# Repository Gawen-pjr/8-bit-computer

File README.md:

# 8-bit-computer
Home made 8 bit computer built from discreet logic components

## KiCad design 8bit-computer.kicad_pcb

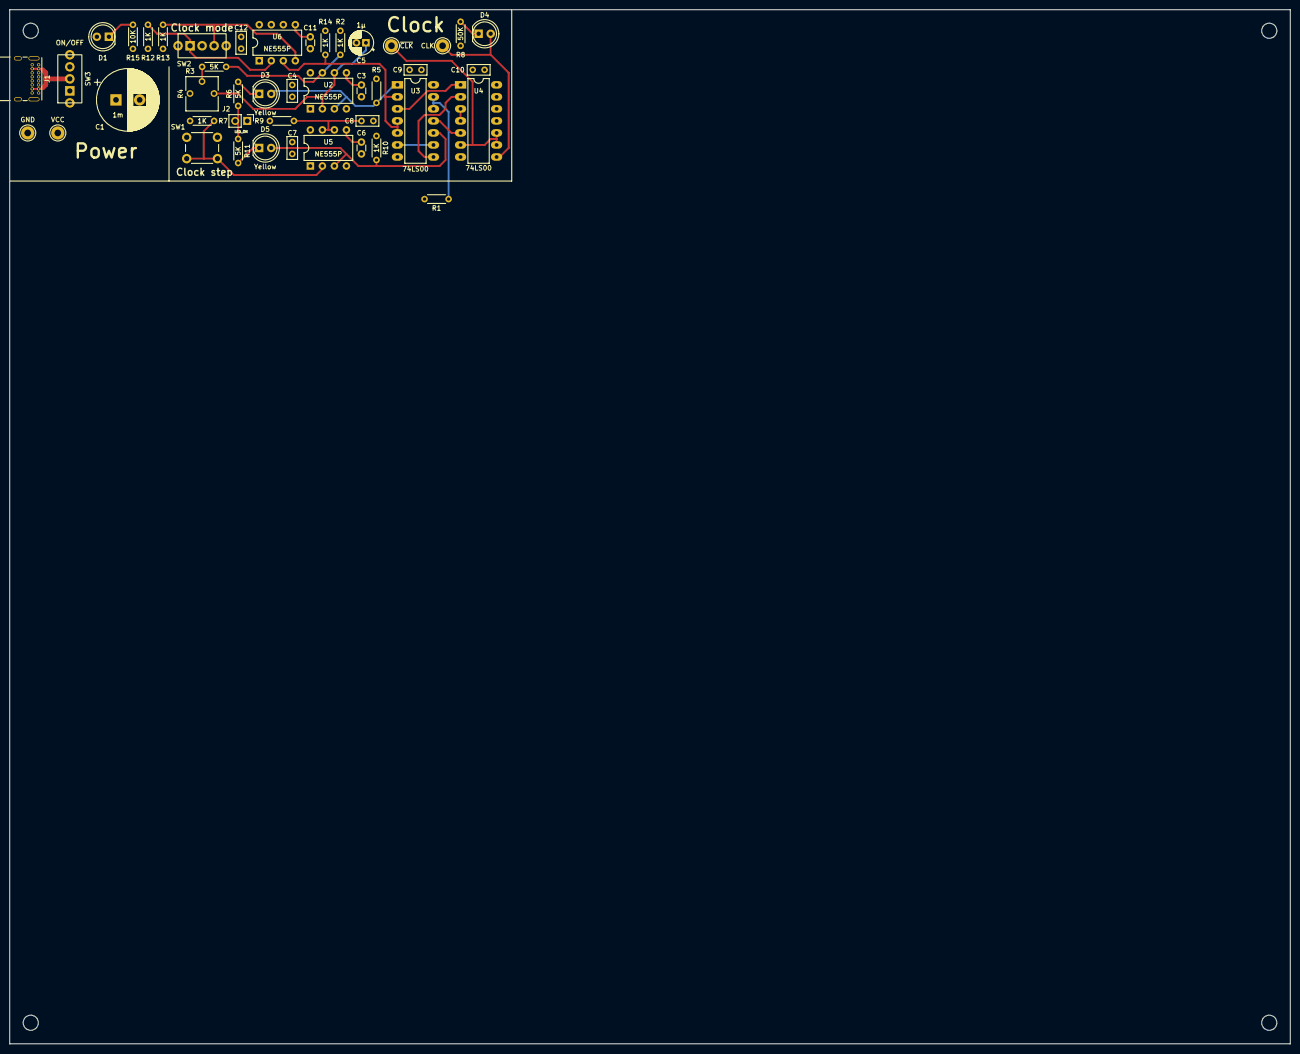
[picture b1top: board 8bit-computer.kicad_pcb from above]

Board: 4 copper layers, 270.5 x 218.4 mm, 48 parts (0 on the bottom side), 29 nets.

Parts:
C1: 1m; CP_Radial_D13.0mm_P5.00mm
C3, C6, C11: 17n; C_Disc_D3.0mm_W1.6mm_P2.50mm
C4, C7, C8, C9, C10, C12: 0.1µ; C_Rect_L4.6mm_W2.0mm_P2.50mm_MKS02_FKP02
C5: 1µ; CP_Radial_D5.0mm_P2.00mm
D1: Red; LED_D5.0mm
D3, D5: Yellow; LED_D5.0mm
D4: Blue; LED_D5.0mm
J1: Power connector; USB_C_Receptacle_GCT_USB4085
J2: LED_ON; PinHeader_1x02_P2.54mm_Vertical
MH1, MH2, MH3, MH4: MountingHole_3.2mm_M3
R1, R2, R5, R7, R10, R12, R13, R14: 1K; R_Axial_DIN0204_L3.6mm_D1.6mm_P5.08mm_Horizontal
R3, R6, R11: 5K; R_Axial_DIN0204_L3.6mm_D1.6mm_P5.08mm_Horizontal
R4: 1.5M; Potentiometer_Vishay_T73YP_Vertical
R8: 50K; R_Axial_DIN0204_L3.6mm_D1.6mm_P5.08mm_Horizontal
R9: 1M; R_Axial_DIN0204_L3.6mm_D1.6mm_P5.08mm_Horizontal
R15: 10K; R_Axial_DIN0204_L3.6mm_D1.6mm_P5.08mm_Horizontal
SW1: Clock step; SW_PUSH_6mm
SW2: Clock mode; MC8MSLP1B06VS2QES
SW3: ON/OFF; MC8MSLP1B06VS2QES
TP1: GND; TestPoint_Loop_D2.60mm_Drill1.4mm_Beaded
TP2: VCC; TestPoint_Loop_D2.60mm_Drill1.4mm_Beaded
TP3: ~{CLK}; TestPoint_Loop_D2.60mm_Drill1.4mm_Beaded
TP4: CLK; TestPoint_Loop_D2.60mm_Drill1.4mm_Beaded
U2, U5, U6: NE555P; DIP-8_W7.62mm
U3, U4: 74LS00; DIP-14_W7.62mm_LongPads

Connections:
+5V: J1.A4 (VBUS), J1.A9 (VBUS), J1.B4 (VBUS), J1.B9 (VBUS), SW3.2 (B)
/Clock/Clk_A: D3.2 (A), R5.2, U2.3 (Q), U3.1
/Clock/Clk_M: D5.2 (A), R10.2, U3.10, U5.3 (Q)
/Clock/HLT: R1.1, U3.12, U3.13
/Clock/LEDs: J2.2, R6.1, R11.1
/Clock/Mode: R14.2, U3.2, U3.4, U3.5, U6.3 (Q)
CLK: D4.2 (A), TP4.1, U4.8
GND: C1.2, C3.2, C4.2, C5.2, C6.2, C7.2, C8.2, C9.2, C10.2, C11.2, C12.2, J1.A1 (GND), J1.A12 (GND), J1.B1 (GND), J1.B12 (GND), J1.S1 (SHIELD), J2.1, R1.2, R8.1, R15.2, SW1.1, SW2.2 (B), TP1.1, U2.1 (GND), U3.7 (GND), U4.7 (GND), U5.1 (GND), U6.1 (GND), U6.6 (THR)
unnamed: C3.1, U2.5 (CV)
unnamed: C5.1, R4.1, U2.2 (TR), U2.6 (THR)
unnamed: C6.1, U5.5 (CV)
unnamed: C8.1, R9.2, U5.6 (THR), U5.7 (DIS)
unnamed: C11.1, U6.5 (CV)
unnamed: D1.1 (K), R15.1
unnamed: D3.1 (K), R6.2
unnamed: D4.1 (K), R8.2
unnamed: D5.1 (K), R11.2
unnamed: R2.2, R3.1, U2.7 (DIS)
unnamed: R3.2, R4.2
unnamed: R7.2, SW1.2, U5.2 (TR)
unnamed: R12.2, SW2.1 (A), U6.2 (TR)
unnamed: R13.1, SW2.3 (C), U6.4 (R)
unnamed: U3.3, U4.1
unnamed: U3.6, U3.9
unnamed: U3.8, U4.2
unnamed: U3.11, U4.5
unnamed: U4.3, U4.4
VCC: C1.1, C4.1, C7.1, C9.1, C10.1, C12.1, D1.2 (A), R2.1, R5.1, R7.1, R9.1, R10.1, R12.1, R13.2, R14.1, SW3.1 (A), TP2.1, U2.4 (R), U2.8 (VCC), U3.14 (VCC), U4.12, U4.13, U4.14 (VCC), U5.4 (R), U5.8 (VCC), U6.8 (VCC)
~CLK: TP3.1, U4.6, U4.9, U4.10

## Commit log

2022-04-20 🎉 import project as-is on 2022-04-20
2022-04-20 🚧 replace power supply with USB-C socket
